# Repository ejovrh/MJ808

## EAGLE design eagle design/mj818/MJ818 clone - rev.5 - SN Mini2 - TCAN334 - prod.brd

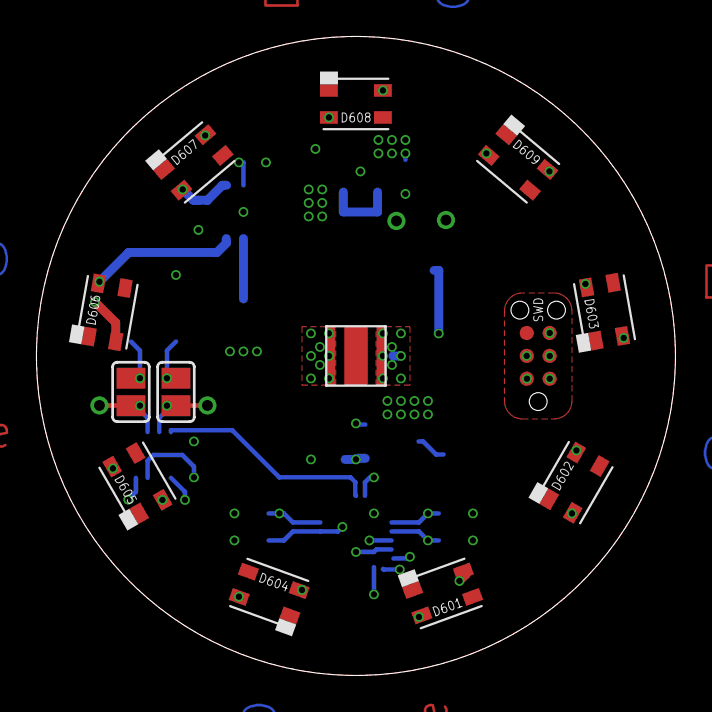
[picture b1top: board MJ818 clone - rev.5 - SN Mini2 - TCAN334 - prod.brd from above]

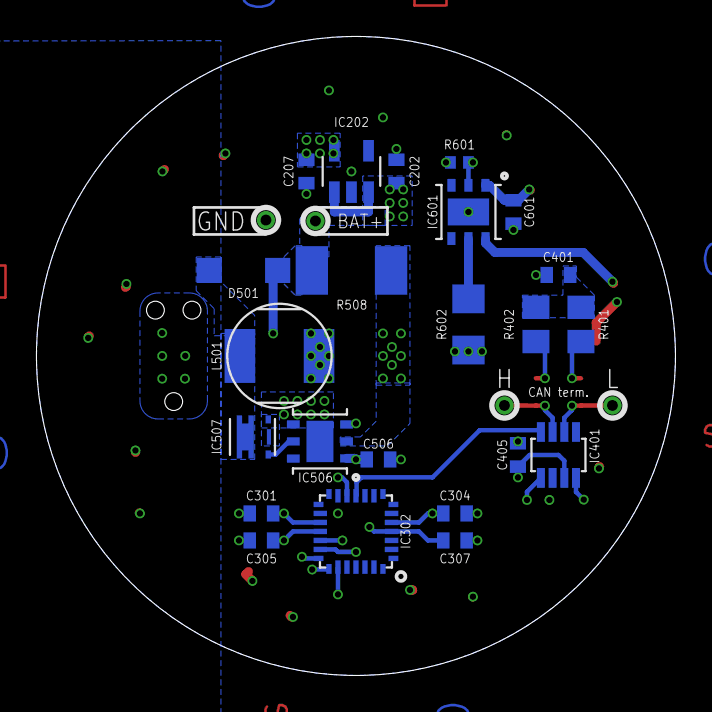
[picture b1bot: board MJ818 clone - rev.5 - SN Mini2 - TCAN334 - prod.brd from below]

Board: 4 copper layers, 35.5 x 35.5 mm, 40 parts (27 on the bottom side), 28 nets.

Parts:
C202, C207, C304, C506, C601: 1uF / 10V; C0402
C301, C305, C307, C405: 0.1uF / 10V; C0402
C401: 47nF / 10V; C0402
D501: PMEG2010ER,115; SOD123
D502: Cree XPERED-L1-R250-00401; SMD
D601, D602, D603, D604, D605, D606, D607, D608, D609: CLM2D-RCC-CZ0B0BB3; SMD
IC202: LDK320AM33R; SOT-23-5L
IC302: STM32F042G6U6; UFQFPN-28
IC401: TCAN334; SOT23-8
IC506: MAX16820; TDFN-6-EP
IC507: SQA470EEJ-T1_GE3; SC-70-6
IC601: MAX16839; TDFN-6-EP
L501: SDE0604A-270M - 27uH; SMT
R401, R402: 60R, 0.5W; R0805
R508: WSLT2010R2200FEB18 / 0.22Ohm 1W; R2010
R601: 10k; R0402
R602: 10R/0.5W; R1206
SJ401: CAN H term.; SJ
SJ402: CAN L term.; SJ
SWD1: TC2030-NL
TP101: LiIon + Terminal; TH-0.6
TP102: LiIon - Terminal; TH-0.6
TP105: CAN high; TH-0.6
TP106: CAN low; TH-0.6

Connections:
3V3: C207.2, C301.2, C304.2, C305.2, C405.1, IC202.OUT, IC302.5_VDDA, IC302.17_VDD, IC302.18_VDDIO2, IC401.P$3, SWD1.1_TVCC
!STBY!: IC302.11_PA5, IC401.P$8
BAT+: C202.1, C506.1, C601.2, D501.C, D601.2, D604.2, D607.2, IC202.EN, IC202.IN, IC506.IN, IC601.IN, R508.2, TP101.TP$1
BRAKE_LED_DRIVER:DIM_BRAKE_DRAIN: D501.A, IC507.1D, IC507.2D, IC507.5D, IC507.6D, IC507.D, L501.P$2
BRAKE_LED_DRIVER:DIM_BRAKE_GATE: IC506.DRV, IC507.3G
BRAKE_LED_DRIVER:LED_AN: D502.AND, IC506.CSN, R508.1
BRAKE_LED_DRIVER:LED_CA: D502.CAT, L501.P$1
CAN_H: IC401.P$7, SJ401.1, TP105.TP$1
CAN_INFRA:H: R402.2, SJ401.2
CAN_INFRA:L: R401.1, SJ402.2
CAN_INFRA:SPLIT: C401.1, R401.2, R402.1
CAN_L: IC401.P$6, SJ402.1, TP106.TP$1
CAN_RX: IC302.19_PA9-[PA11], IC401.P$4
CAN_TX: IC302.20_PA10-[PA12], IC401.P$1
DIM_BRAKE: IC302.12_PA6, IC506.DIM
DIM_REAR: IC302.23_PA15, IC601.DIM, R601.2
GND: C202.2, C207.1, C301.1, C304.1, C305.1, C307.1, C401.2, C405.2, C506.2, C601.1, IC202.GND, IC302.16_VSS, IC401.P$2, IC506.GND, IC506.GND1, IC507.4S, IC507.S, IC601.FLTS, IC601.GND, IC601.GND1, R601.1, R602.2, SWD1.5_GND, TP102.TP$1
REAR_LED_DRIVER:CS: IC601.CS, R602.1
REAR_LED_DRIVER:D1,D2: D601.4, D602.2
REAR_LED_DRIVER:D2,D3: D602.4, D603.2
REAR_LED_DRIVER:D4,D5: D604.4, D605.2
REAR_LED_DRIVER:D5,D6: D605.4, D606.2
REAR_LED_DRIVER:D7,D8: D607.4, D608.2
REAR_LED_DRIVER:D8,D9: D608.4, D609.2
REAR_LED_DRIVER:SINK: D603.4, D606.4, D609.4, IC601.SINK
SYS_NRST: C307.2, IC302.4_NRST, SWD1.3_T_NRST
SYS_SWCLK: IC302.22_PA14, SWD1.4_T_SWCLK
SYS_SWDIO: IC302.21_PA13, SWD1.2_T_SWDIO

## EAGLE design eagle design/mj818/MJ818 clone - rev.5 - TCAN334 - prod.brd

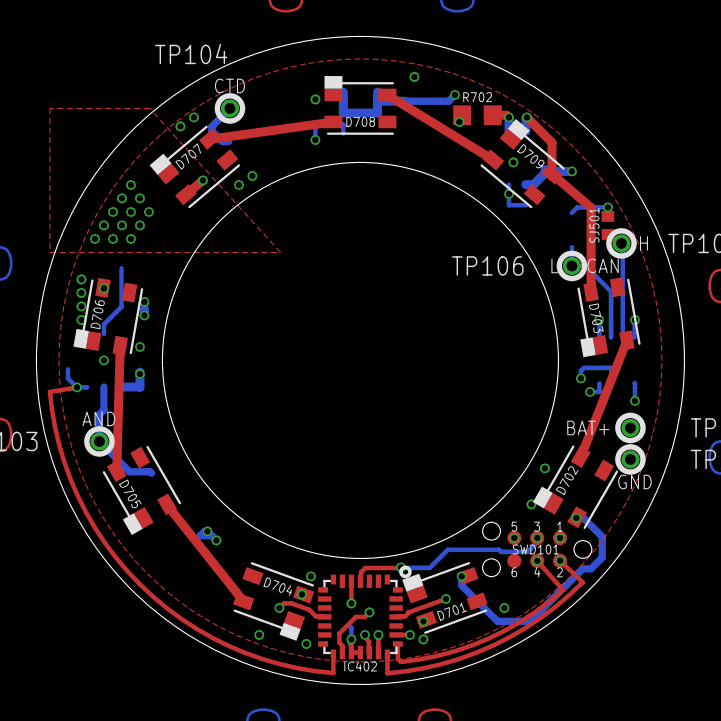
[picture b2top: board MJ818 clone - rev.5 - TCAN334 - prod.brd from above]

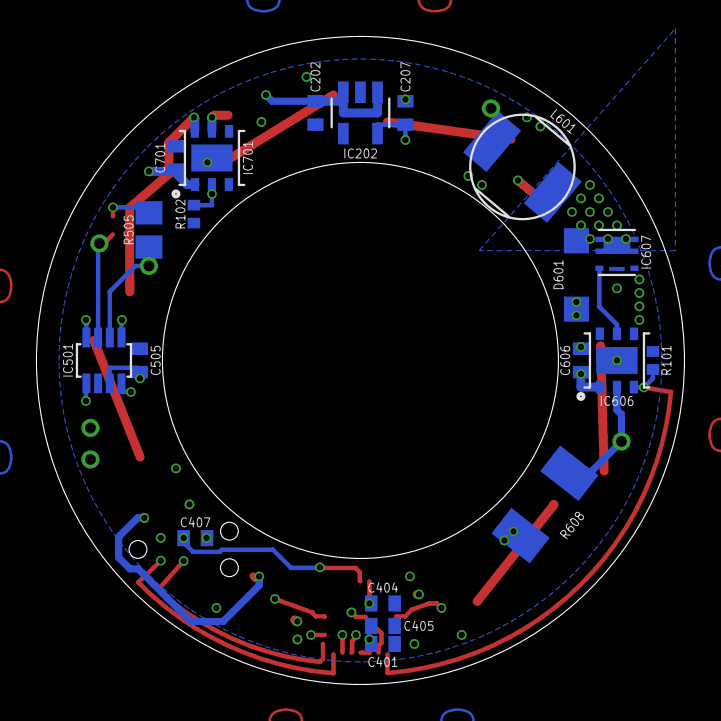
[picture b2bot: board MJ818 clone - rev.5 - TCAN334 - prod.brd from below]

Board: 4 copper layers, 36.0 x 36.0 mm, 39 parts (20 on the bottom side), 27 nets.

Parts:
C202, C606: 1μF / 10V; C0402
C207, C701: 1μF; C0402
C401, C405, C407: 0.1u; C0402
C404: 1u; C0402
C505: 0.1μF; C0402
D601: PMEG2010ER,115; SOD123
D701, D702, D703, D704, D705, D706, D707, D708, D709: CLM2D-RCC-CZ0B0BB3; SMD
IC202: LDK320AM33R; SOT-23-5L
IC402: STM32F042G6U6; UFQFPN-28
IC501: TCAN334; SOT23-8
IC606: MAX16820; TDFN-6-EP
IC607: SQA470EEJ-T1_GE3; SC-70-6
IC701: MAX16839; TDFN-6-EP
L601: SDE0604A-270M - 27uH; SMT
R101, R102: 10k; R0402
R505: 120; R0805
R608: WSLT2010R2200FEB18 / 0.22Ohm 1W; R2010
R702: 10R/0.5W; R0603
SJ501: CAN termination; R0402
SWD101: TC2030-NL
TP101: LiIon + Terminal; TH
TP102: LiIon - Terminal; TH
TP103: LED anode; TH
TP104: LED cathode; TH
TP105: CAN high; TH
TP106: CAN low; TH

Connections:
3V3: C207.2, C401.2, C404.2, C405.2, C505.1, IC202.OUT, IC402.5_VDDA, IC402.17_VDD, IC402.18_VDDIO2, IC501.P$3, SWD101.1_TVCC
!SHDN!: IC402.25_PB4, IC501.P$5
!STBY!: IC402.11_PA5, IC501.P$8
BAT+: C202.1, C606.1, C701.2, D601.C, D701.2, D704.2, D707.2, IC202.EN, IC202.IN, IC606.IN, IC701.IN, R608.2, TP101.TP$1
BRAKE_LED_DRIVER:DIM_BRAKE_DRAIN: D601.A, IC607.1D, IC607.2D, IC607.5D, IC607.6D, IC607.D, L601.P$2
BRAKE_LED_DRIVER:DIM_BRAKE_GATE: IC606.DRV, IC607.3G
CAN_H: IC501.P$7, SJ501.2, TP105.TP$1
CAN_INFRA:CAN_JMPR: R505.2, SJ501.1
CAN_L: IC501.P$6, R505.1, TP106.TP$1
CAN_RX: IC402.19_PA9-[PA11], IC501.P$4
CAN_TX: IC402.20_PA10-[PA12], IC501.P$1
DIM_BRAKE: IC402.15_PB1, IC606.DIM, R101.2
DIM_REAR: IC402.23_PA15, IC701.DIM, R102.2
GND: C202.2, C207.1, C401.1, C404.1, C405.1, C407.1, C505.2, C606.2, C701.1, IC202.GND, IC402.16_VSS, IC501.P$2, IC606.GND, IC606.GND1, IC607.4S, IC607.S, IC701.FLTS, IC701.GND, IC701.GND1, R101.1, R102.1, R702.2, SWD101.5_GND, TP102.TP$1
LED_AN: IC606.CSN, R608.1, TP103.TP$1
LED_CA: L601.P$1, TP104.TP$1
REAR_LED_DRIVER:CS: IC701.CS, R702.1
REAR_LED_DRIVER:D1,D2: D701.4, D702.2
REAR_LED_DRIVER:D2,D3: D702.4, D703.2
REAR_LED_DRIVER:D4,D5: D704.4, D705.2
REAR_LED_DRIVER:D5,D6: D705.4, D706.2
REAR_LED_DRIVER:D7,D8: D707.4, D708.2
REAR_LED_DRIVER:D8,D9: D708.4, D709.2
REAR_LED_DRIVER:SINK: D703.4, D706.4, D709.4, IC701.SINK
SYS_NRST: C407.2, IC402.4_NRST, SWD101.3_T_NRST
SYS_SWCLK: IC402.22_PA14, SWD101.4_T_SWCLK
SYS_SWDIO: IC402.21_PA13, SWD101.2_T_SWDIO

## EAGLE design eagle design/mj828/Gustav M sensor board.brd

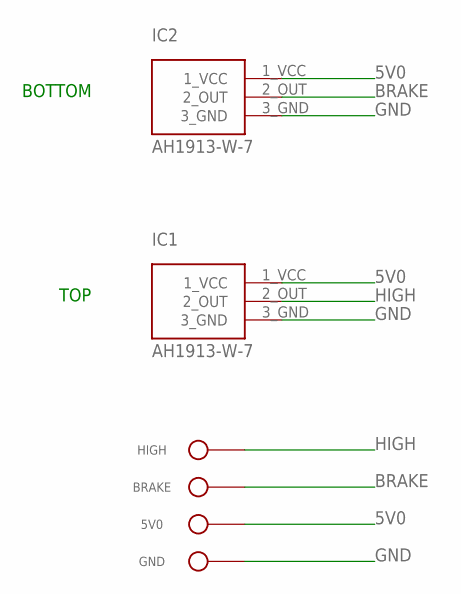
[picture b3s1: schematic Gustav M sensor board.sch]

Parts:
5V0: 8V4 Battery +; TH-0.9MM
BRAKE: 8V4 Battery +; TH-0.9MM
GND: 8V4 Battery +; TH-0.9MM
HIGH: 8V4 Battery +; TH-0.9MM
IC1, IC2: AH1913-W-7; SC59-3

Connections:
5V0: 5V0.TP$1, IC1.1_VCC, IC2.1_VCC
BRAKE: BRAKE.TP$1, IC2.2_OUT
GND: GND.TP$1, IC1.3_GND, IC2.3_GND
HIGH: HIGH.TP$1, IC1.2_OUT

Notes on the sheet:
TOP
BOTTOM

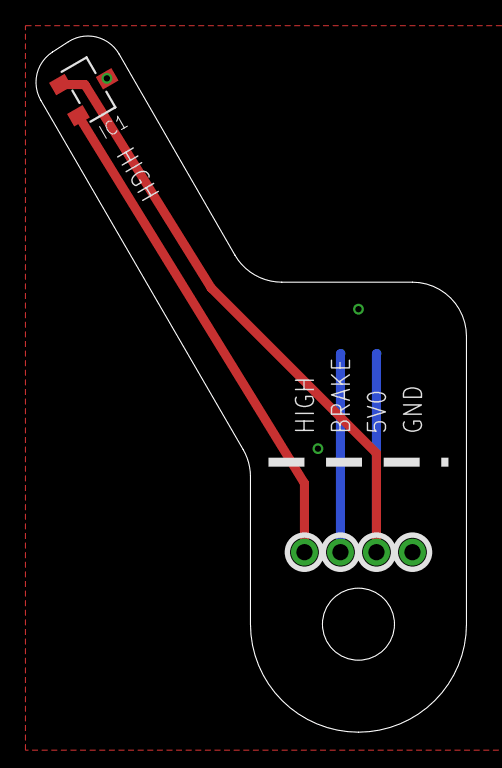
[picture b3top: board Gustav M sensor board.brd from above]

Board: 2 copper layers, 23.9 x 38.7 mm, 6 parts (1 on the bottom side), 4 nets.

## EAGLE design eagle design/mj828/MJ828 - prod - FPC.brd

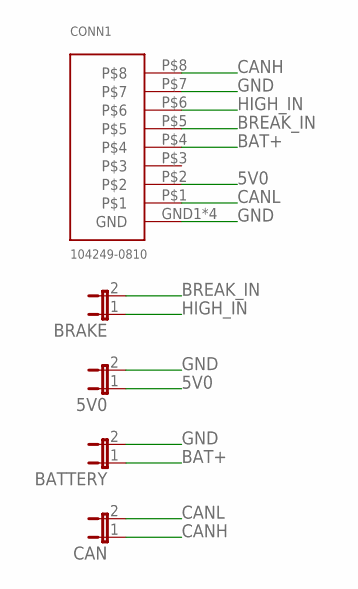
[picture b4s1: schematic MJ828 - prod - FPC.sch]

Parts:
5V0: JP1E; JP1
BATTERY: JP1E; JP1
BRAKE: JP1E; JP1
CAN: JP1E; JP1
CONN1: 104249-0810; SMD

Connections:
5V0: 5V0.1, CONN1.P$2
BAT+: BATTERY.1, CONN1.P$4
BREAK_IN: BRAKE.2, CONN1.P$5
CANH: CAN.1, CONN1.P$8
CANL: CAN.2, CONN1.P$1
GND: 5V0.2, BATTERY.2, CONN1.GND1 (GND), CONN1.GND2 (GND), CONN1.GND3 (GND), CONN1.GND4 (GND), CONN1.P$7
HIGH_IN: BRAKE.1, CONN1.P$6

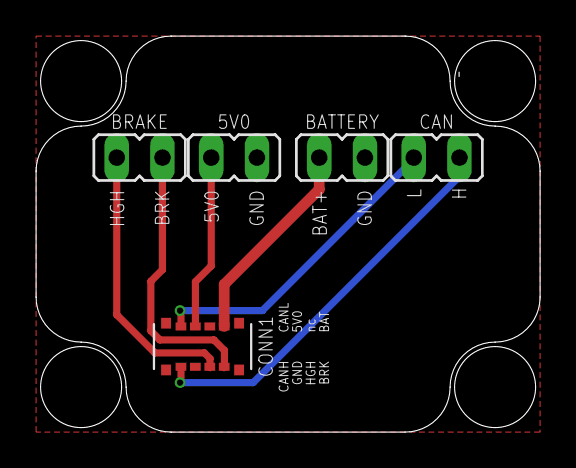
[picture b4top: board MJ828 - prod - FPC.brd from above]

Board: 2 copper layers, 28.0 x 22.0 mm, 5 parts (0 on the bottom side), 7 nets.

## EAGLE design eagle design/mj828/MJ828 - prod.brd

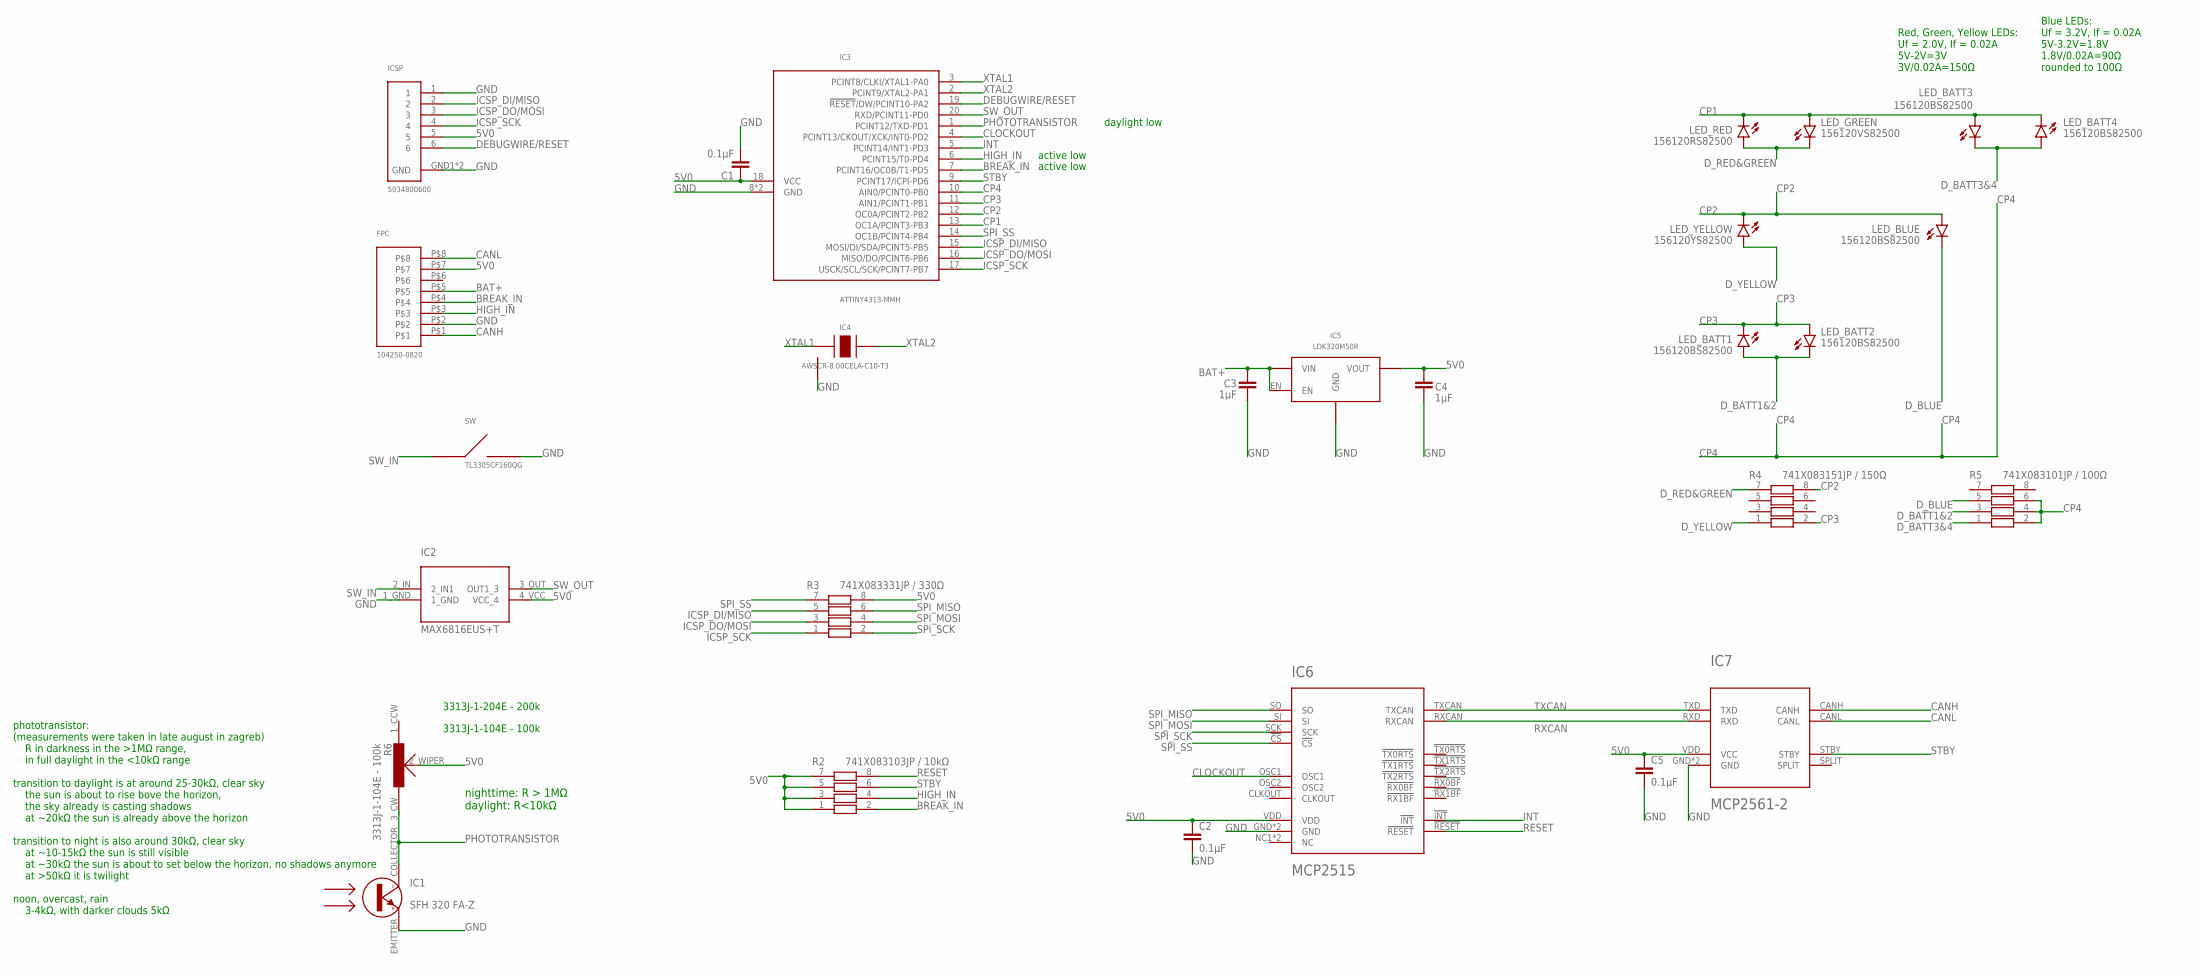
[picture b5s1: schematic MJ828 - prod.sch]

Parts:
C1, C2, C5: 0.1μF; C0402
C3, C4: 1μF; C0402
FPC: 104250-0820; SMD
IC1: SFH 320 FA-Z; P-LCC-2
IC2: MAX6816EUS+T; 4SOT143
IC3: ATTINY4313-MMH; VQFN-20
IC4: AWSCR-8.00CELA-C10-T3; SMT
IC5: LDK320M50R; SOT-23-5L
IC6: MCP2515; QFN20
IC7: MCP2561-2; DFN10
ICSP: 5034800600; SMT
LED_BATT1, LED_BATT2, LED_BATT3, LED_BATT4: 156120BS82500; SML1206
LED_BLUE: 156120BS82500; SML1206
LED_GREEN: 156120VS82500; SML1206
LED_RED: 156120RS82500; SML1206
LED_YELLOW: 156120YS82500; SML1206
R2: 741X083103JP / 10kΩ; 0402
R3: 741X083331JP / 330Ω; 0402
R4: 741X083151JP / 150Ω; 0402
R5: 741X083101JP / 100Ω; 0402
R6: 3313J-1-104E - 100k; 3313
SW: TL3305CF160QG; SMD

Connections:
5V0: C1.1, C2.1, C4.2, C5.1, FPC.P$7, IC2.4_VCC (VCC_4), IC3.18 (VCC), IC5.OUT (VOUT), IC6.VDD, IC7.VDD (VCC), ICSP.5, R2.1, R2.3, R2.5, R2.7, R3.8, R6.2_WIPER
BAT+: C3.1, FPC.P$5, IC5.EN, IC5.IN (VIN)
BREAK_IN: FPC.P$4, IC3.7 (PCINT16/OC0B/T1-PD5), R2.2
CANH: FPC.P$1, IC7.CANH
CANL: FPC.P$8, IC7.CANL
CLOCKOUT: IC3.4 (PCINT13/CKOUT/XCK/INT0-PD2), IC6.OSC1
CP1: IC3.13 (OC1A/PCINT3-PB3), LED_BATT3.A, LED_BATT4.C, LED_GREEN.A, LED_RED.C
CP2: IC3.12 (OC0A/PCINT2-PB2), LED_BLUE.A, LED_YELLOW.C, R4.8
CP3: IC3.11 (AIN1/PCINT1-PB1), LED_BATT1.C, LED_BATT2.A, R4.2
CP4: IC3.10 (AIN0/PCINT0-PB0), R5.2, R5.4, R5.6
DEBUGWIRE/RESET: IC3.19 (!RESET!/DW/PCINT10-PA2), ICSP.6
D_BATT1&2: LED_BATT1.A, LED_BATT2.C, R5.3
D_BATT3&4: LED_BATT3.C, LED_BATT4.A, R5.1
D_BLUE: LED_BLUE.C, R5.5
D_RED&GREEN: LED_GREEN.C, LED_RED.A, R4.7
D_YELLOW: LED_YELLOW.A, R4.1
GND: C1.2, C2.2, C3.2, C4.1, C5.2, FPC.P$2, IC1.EMITTER, IC2.1_GND, IC3.8 (GND), IC3.GND, IC4.GND, IC5.GND, IC6.GND, IC6.GND6 (GND), IC7.GND, IC7.VSS (GND), ICSP.1, ICSP.GND1 (GND), ICSP.GND2 (GND), SW.3, SW.4
HIGH_IN: FPC.P$3, IC3.6 (PCINT15/T0-PD4), R2.4
ICSP_DI/MISO: IC3.15 (MOSI/DI/SDA/PCINT5-PB5), ICSP.2, R3.5
ICSP_DO/MOSI: IC3.16 (MISO/DO/PCINT6-PB6), ICSP.3, R3.3
ICSP_SCK: IC3.17 (USCK/SCL/SCK/PCINT7-PB7), ICSP.4, R3.1
INT: IC3.5 (PCINT14/INT1-PD3), IC6.!INT!
PHOTOTRANSISTOR: IC1.COLLECTOR, IC3.1 (PCINT12/TXD-PD1), R6.3_CW
RESET: IC6.!RESET!, R2.8
RXCAN: IC6.RXCAN, IC7.RXD
SPI_MISO: IC6.SO, R3.6
SPI_MOSI: IC6.SI, R3.4
SPI_SCK: IC6.SCK, R3.2
SPI_SS: IC3.14 (OC1B/PCINT4-PB4), IC6.!CS!, R3.7
STBY: IC3.9 (PCINT17/ICPI-PD6), IC7.STBY, R2.6
SW_IN: IC2.2_IN (2_IN1), SW.1, SW.2
SW_OUT: IC2.3_OUT (OUT1_3), IC3.20 (RXD/PCINT11-PD0)
TXCAN: IC6.TXCAN, IC7.TXD
XTAL1: IC3.3 (PCINT8/CLKI/XTAL1-PA0), IC4.XTAL1
XTAL2: IC3.2 (PCINT9/XTAL2-PA1), IC4.XTAL2

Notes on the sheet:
Red, Green, Yellow LEDs: Uf = 2.0V, If = 0.02A 5V-2V=3V 3V/0.02A=150Ω
Blue LEDs: Uf = 3.2V, If = 0.02A 5V-3.2V=1.8V 1.8V/0.02A=90Ω rounded to 100Ω
phototransistor: (measurements were taken in late august in zagreb) R in darkness in the >1MΩ range, in full daylight in the <10kΩ range transition to daylight is at around 25-30kΩ, clear sky the sun is about to rise bove the horizon, the sky already is casting shadows at ~20kΩ the sun is already a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
nighttime: R > 1MΩ daylight: R<10kΩ
3313J-1-204E - 200k
3313J-1-104E - 100k
active low
daylight low

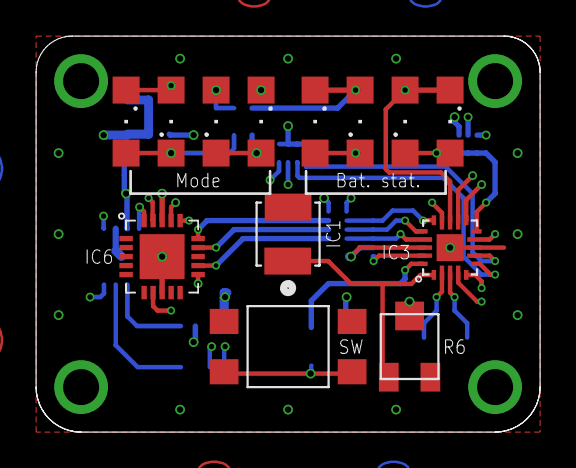
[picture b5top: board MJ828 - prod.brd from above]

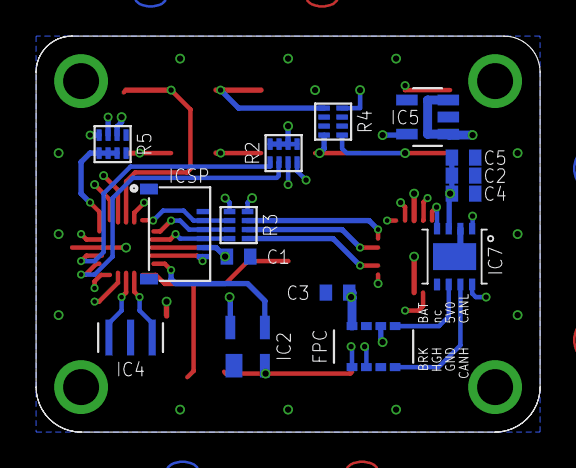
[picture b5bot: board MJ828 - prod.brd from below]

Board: 4 copper layers, 28.0 x 22.0 mm, 28 parts (15 on the bottom side), 35 nets.

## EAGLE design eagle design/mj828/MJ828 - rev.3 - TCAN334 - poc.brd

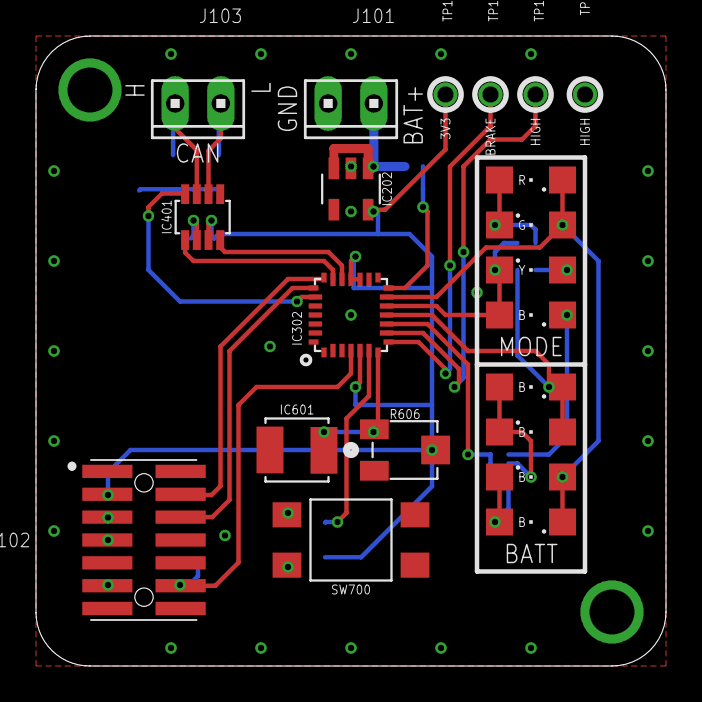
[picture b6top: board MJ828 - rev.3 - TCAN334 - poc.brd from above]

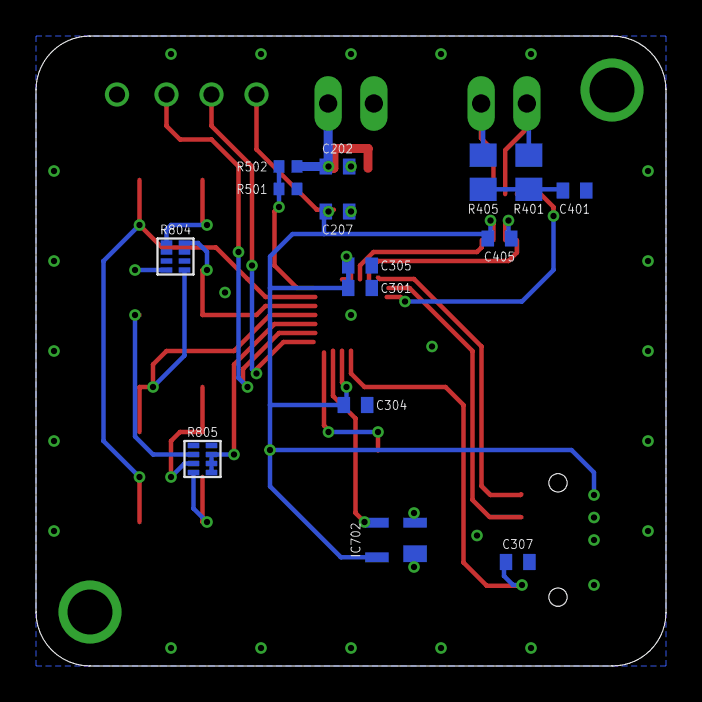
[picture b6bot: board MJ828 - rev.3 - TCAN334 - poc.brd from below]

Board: 2 copper layers, 35.0 x 35.0 mm, 36 parts (15 on the bottom side), 27 nets.

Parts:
C202, C207, C304: 1uF / 10V; C0402
C301, C305, C307, C405: 0.1uF / 10V; C0402
C401: 47nF / 10V; C0402
IC202: LDK320AM33R; SOT-23-5L
IC302: STM32F042G6U6; UFQFPN-28
IC401: TCAN334; SOT23-8
IC601: SFH 320 FA-Z; P-LCC-2
IC702: MAX6816EUS+T; 4SOT143
J101: Power Supply; 10X02MTA
J102: FTSH-107-01-L-DV-K-A; FTSH10701LDVKA
J103: CAN; 10X02MTA
LED_BATT801, LED_BATT802, LED_BATT803, LED_BATT804: 156120BS82500; SML1206
LED_BLUE800: 156120BS82500; SML1206
LED_GREEN800: 156120VS82500; SML1206
LED_RED800: 156120RS82500; SML1206
LED_YELLOW800: 156120YS82500; SML1206
R401, R405: 60; R0805
R501: 100k 0.1%; R0402
R502: 300k 0.1%; R0402
R606: 3313J-1-104E - 100k; 3313
R804: 741X083151JP / 150Ω; 0402
R805: 741X083101JP / 100Ω; 0402
SW700: TL3305CF160QG; SMD
TP1, TP102, TP104, TP105: CAN low; TH-0.9

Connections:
3V3: C207.2, C301.2, C304.2, C305.2, C405.1, IC202.OUT, IC302.5_VDDA, IC302.17_VDD, IC302.18_VDDIO2, IC401.P$3, IC702.4_VCC, J102.3, R606.2_WIPER, TP102.P$1
!STBY!: IC302.23_PA15, IC401.P$8
BAT+: C202.1, IC202.EN, IC202.IN, J101.2, R502.2
BREAK_IN: IC302.8_PA2, TP104.P$1
CAN_H: IC401.P$7, J103.1, R401.2
CAN_INFRA:SPLIT: C401.1, R401.1, R405.2
CAN_L: IC401.P$6, J103.2, R405.1
CAN_RX: IC302.19_PA9-[PA11], IC401.P$4
CAN_TX: IC302.20_PA10-[PA12], IC401.P$1
CP1: IC302.13_PA7, LED_BATT803.A, LED_BATT804.C, LED_GREEN800.A, LED_RED800.C
CP2: IC302.12_PA6, LED_BLUE800.A, LED_YELLOW800.C, R804.8
CP3: IC302.11_PA5, LED_BATT801.C, LED_BATT802.A, R804.2
CP4: IC302.10_PA4, R805.2, R805.4, R805.6
GND: C202.2, C207.1, C301.1, C304.1, C305.1, C307.1, C401.2, C405.2, IC202.GND, IC302.16_VSS, IC401.P$2, IC601.EMITTER, IC702.1_GND, J101.1, J102.5, J102.7, J102.11, R501.1, SW700.3, SW700.4, TP1.P$1
HIGH_IN: IC302.9_PA3, TP105.P$1
LED:D_BATT1&2: LED_BATT801.A, LED_BATT802.C, R805.3
LED:D_BATT3&4: LED_BATT803.C, LED_BATT804.A, R805.1
LED:D_BLUE: LED_BLUE800.C, R805.5
LED:D_RED&GREEN: LED_GREEN800.C, LED_RED800.A, R804.7
LED:D_YELLOW: LED_YELLOW800.A, R804.1
PHOTOTRANSISTOR: IC302.7_PA1, IC601.COLLECTOR, R606.3_CW
PUSHBUTTON: IC302.6_PA0, IC702.3_OUT
PUSHBUTTON:SWITCH_IN: IC702.2_IN, SW700.1, SW700.2
SYS_NRST: C307.2, IC302.4_NRST, J102.12
SYS_SWCLK: IC302.22_PA14, J102.6
SYS_SWDIO: IC302.21_PA13, J102.4
VBAT+: IC302.14_PB0, R501.2, R502.1

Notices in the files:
parts and their libraries:
tag-connect: ©2009 ROFA.cz - modified and updated by Robert Darlington ‹rdarlington@gmail.com›
